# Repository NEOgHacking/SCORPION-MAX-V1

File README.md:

# 3D printer / CNC Mainboard

A main board for a 3d printer or CNC with wide possibilities with the use of the expansion board and thermistor boards! This board is based on the STM32H743 for its massive power. And everyone hates loud stepper motors, so it uses the TMC2130 silent stepper drivers, these are not only very quiet but have a lot of other functions!

# Video of working

# Reason
So long story longer I have an ultimaker 2+ laying at home doing nothing because of the noisy stepper drivers and recently getting an ultimaker S5 so I wanted to make it quieter and more useful. I was amazed by the Prusa mini being so quiet, so I thought why not build my own mainboard with way more quiet stepper drivers and more functions. The second reason is that I am planning to build a CNC somewhere in the future so I thought it would be a genius idea to build my own 3D printer / CNC mainboard with my own overkill specs and the best stepper drivers. And most of all A LOT of power in amps and compute!

# Specs
5x Stepper driver TMC2130

4x Power Mosfets for controlling heated beds, heaters, ext.

4x Fan controller with tacho input

4x Limit switches for homing

3x Thermistor inputs with possibilities for NTC's and PTC's
  These possibilities are possible because of the 2 thermistor boards I have designed, and the NTC thermistor board has a solder jumper to select the resistance of you NTC.

2x Safety inputs for disabling cutting power via a relay to the stepper drivers and mosfets

Expansion port for displays, SD cards, ext.

STM32H743VIT6 for big storage and calculation power

Standard 4 pin power connector and 2 pin screw terminal

USB ports, USB-C for programming and external control and USB-A for USB flash drives

# Design
This board is designed with a lot of safety features and well thought out design, it has a safety circuit to cut power to the steppers and heaters, good pcb design, followed design recommendation from datasheets, used the right components, and allot more! The pcb has been designed with the right trace width and good trace layout with no sharp bends. Also have good pcb layout.
# Schematics
There are 3 schematics for this project:
1. Main board
2. Thermistor modules
3. Expansion module

These are way too long to display here (14 pages) so in the PCB folder there in folder for the board you want to see there is a pdf file of the schematic, but here are a few.

# PCB

Main board

Thermistor boards

Expansion board

# Panalization
I have panelized the thermistor boards for better price per board, the panel still is under the 100x100 limit for the 2 dollar offer on jlcpcb so it’s still very cheap. I needed 6 thermistors for 2 boards and minimum order quantity on jlcpcb is 5, so I made a panel.

# Firmware
The firmware provided is Marlin, but I plan to expand this to more firmware’s like Clipper ext. The board is based on the STM32H743 so it's very powerful and can run almost any firmware!

# BOM
I have made a BOM for LCSC and a global BOM for all the parts and PCBs these are in the BOM folder
The price of the LCSC BOM for all the parts is about 180 dollars for 2 boards and the JLCPCB order is at the 54 dollar.
This is not the cheapest board but it does have the most functions!

# Credits
@Kai Pereira for all my random questions regarding PCB design and blueprint custom project. and for telling me long journals are the best, sorry for the short ones at the beginning. whoops.
Henk, someone I know that is way better in PCB design than me that looked over my schematic and layout ext.

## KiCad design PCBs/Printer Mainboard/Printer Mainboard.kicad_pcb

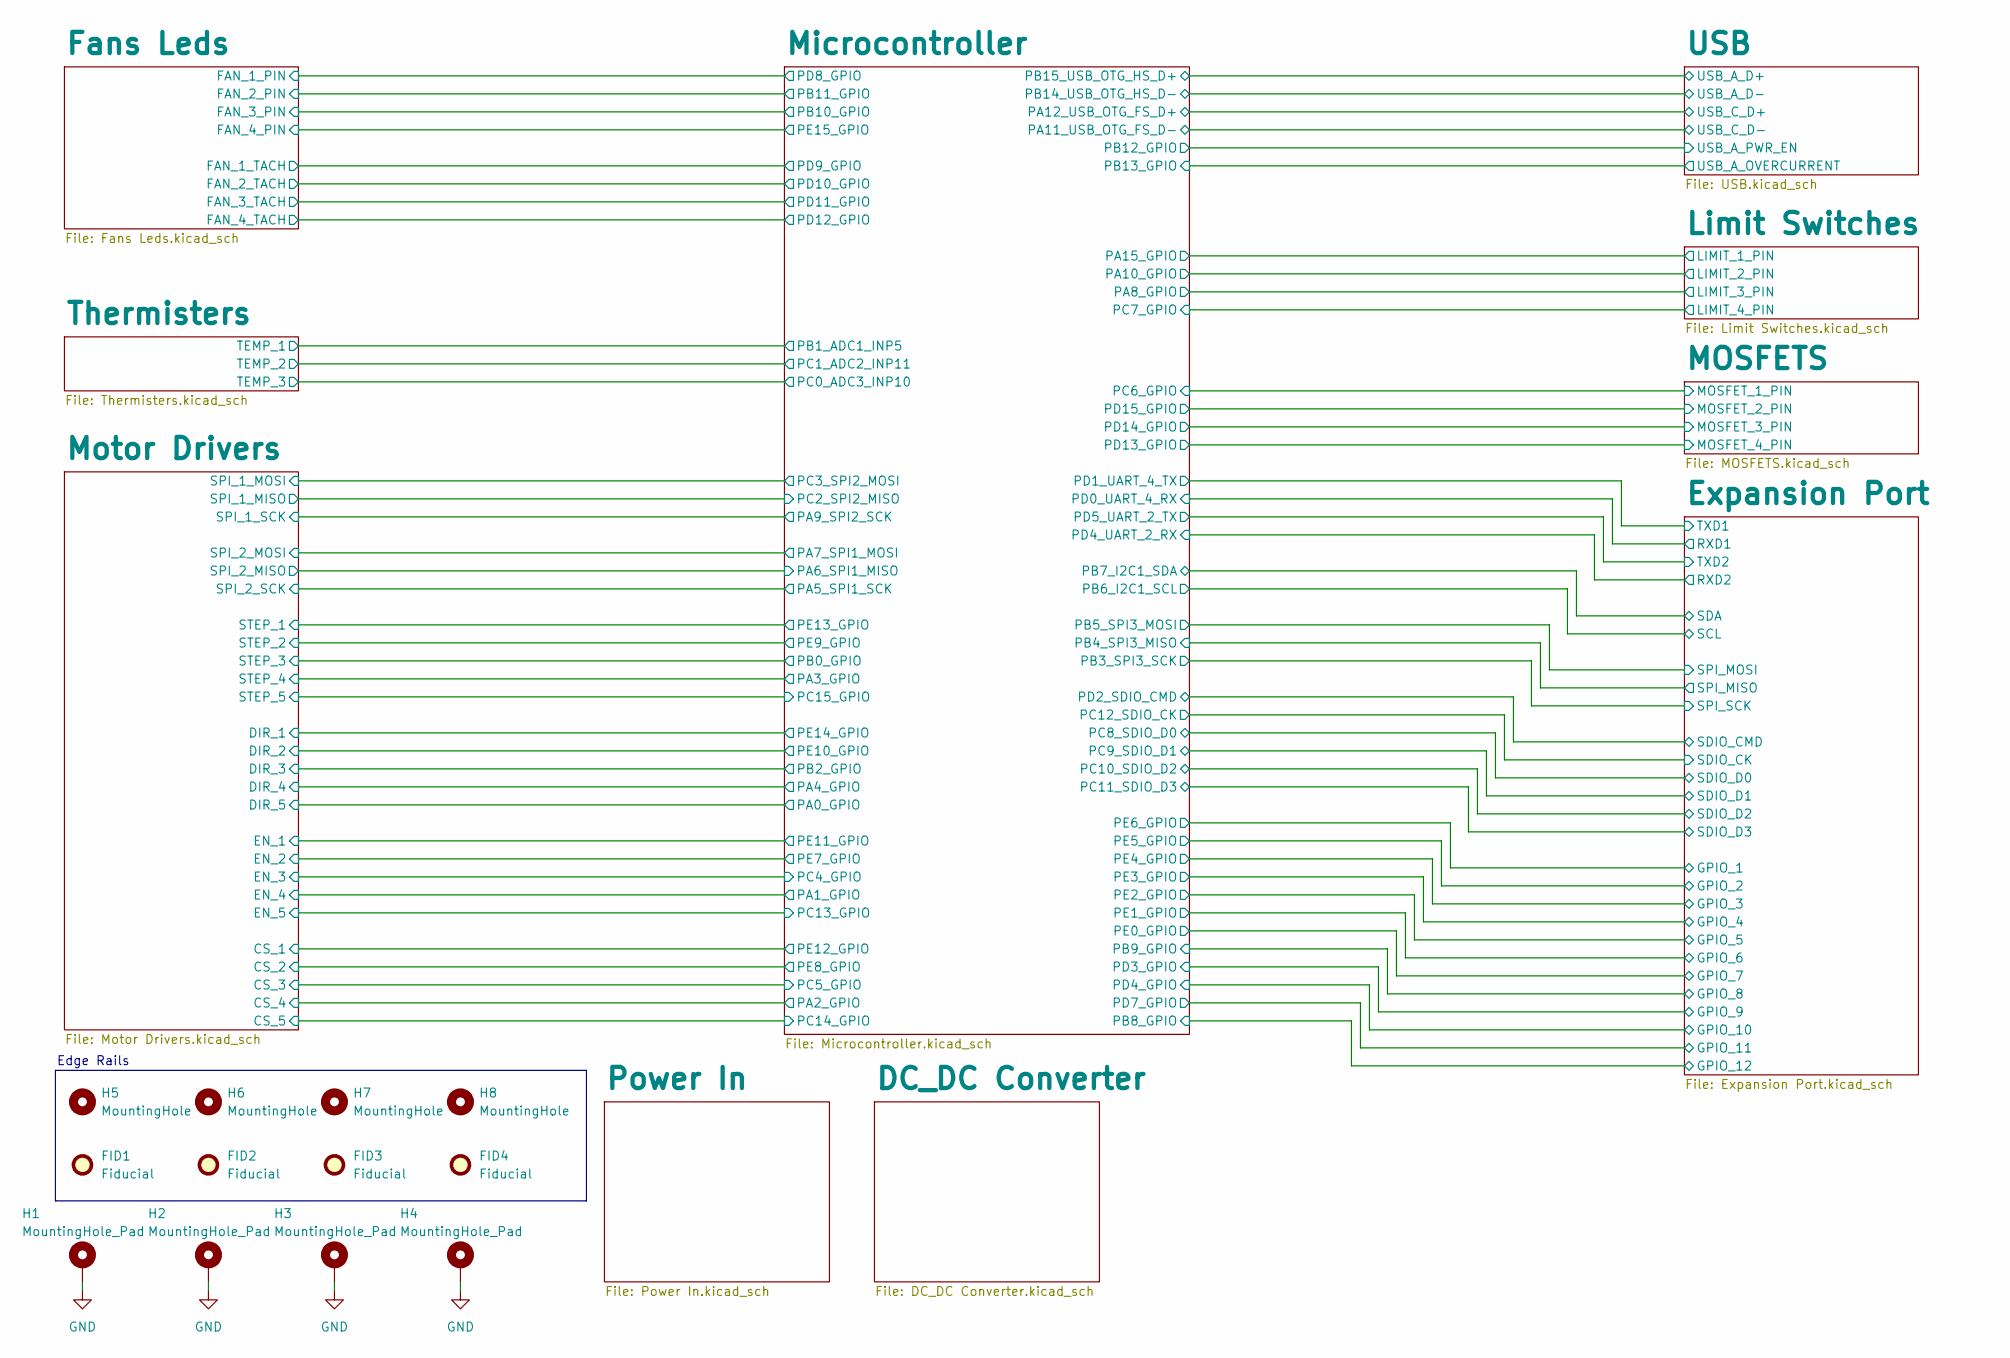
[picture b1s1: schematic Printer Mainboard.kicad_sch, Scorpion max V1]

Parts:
FID1, FID2, FID3, FID4: Fiducial; Fiducial_0.5mm_Mask1.5mm
H1, H2, H3, H4: MountingHole_Pad; MountingHole_3.2mm_M3_Pad
H5, H6, H7, H8: MountingHole; MountingHole_2mm

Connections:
GND: H1.1, H2.1, H3.1, H4.1; also elsewhere on the board

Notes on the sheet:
Edge Rails

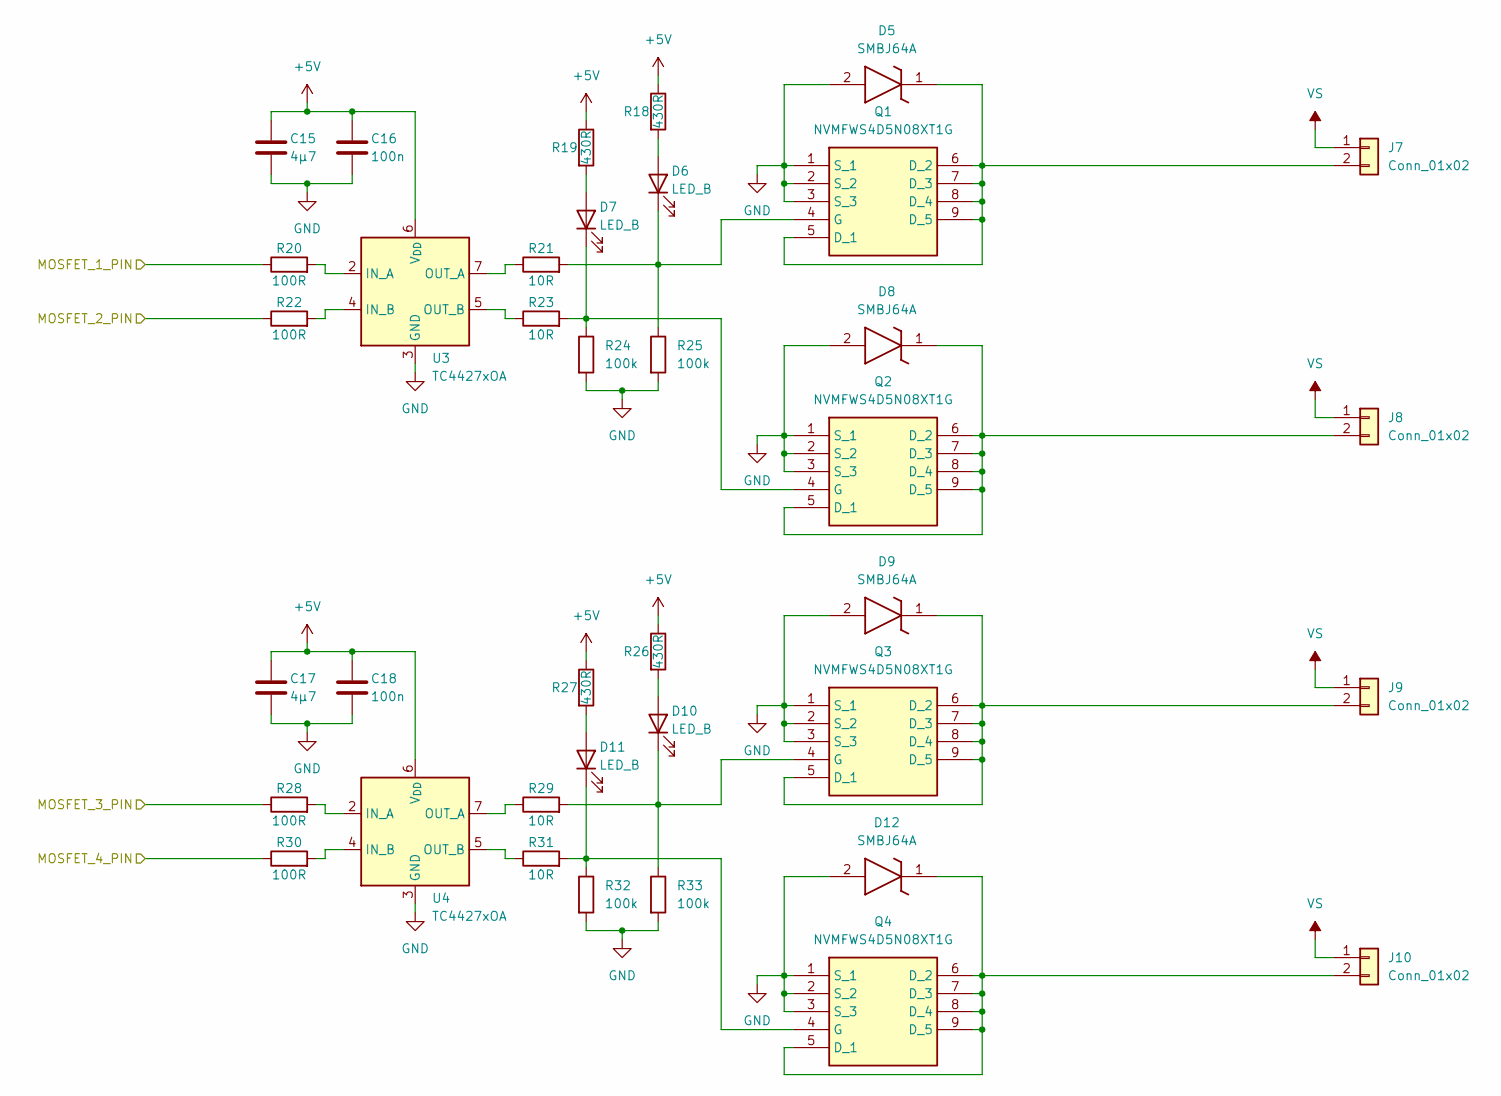
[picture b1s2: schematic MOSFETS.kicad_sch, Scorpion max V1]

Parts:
C15, C17: 4μ7; C_0805_2012Metric
C16, C18: 100n; C_0603_1608Metric
D5, D8, D9, D12: SMBJ64A; DIOM5436X250N; Manufacturer_Part_Number SMBJ64A
D6, D7, D10, D11: LED_B; LED_0603_1608Metric
J7, J8, J9, J10: Conn_01x02; CONN-TH_2P-P5.08_2EDG-5.08-2AW
Q1, Q2, Q3, Q4: NVMFWS4D5N08XT1G; NVMFS5C460NWFT1G; Mouser Part Number 863-NVMFWS4D5N08XT1G
R18, R19, R26, R27: 430R; R_0603_1608Metric
R20, R22, R28, R30: 100R; R_0603_1608Metric
R21, R23, R29, R31: 10R; R_0805_2012Metric
R24, R25, R32, R33: 100k; R_0603_1608Metric
U3, U4: TC4427xOA; SOIC-8_3.9x4.9mm_P1.27mm

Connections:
+5V: C15.1, C16.1, C17.1, C18.1, R18.1, R19.1, R26.1, R27.1, U3.6 (V_{DD}), U4.6 (V_{DD}); also elsewhere on the board
/MOSFETS/MOSFET_1_PIN: R20.1; also elsewhere on the board
/MOSFETS/MOSFET_2_PIN: R22.1; also elsewhere on the board
/MOSFETS/MOSFET_3_PIN: R28.1; also elsewhere on the board
/MOSFETS/MOSFET_4_PIN: R30.1; also elsewhere on the board
GND: C15.2, C16.2, C17.2, C18.2, D5.2 (A), D8.2 (A), D9.2 (A), D12.2 (A), Q1.1 (S_1), Q1.2 (S_2), Q1.3 (S_3), Q2.1 (S_1), Q2.2 (S_2), Q2.3 (S_3), Q3.1 (S_1), Q3.2 (S_2), Q3.3 (S_3), Q4.1 (S_1), Q4.2 (S_2), Q4.3 (S_3), R24.2, R25.2, R32.2, R33.2, U3.3 (GND), U4.3 (GND); also elsewhere on the board
unnamed: D5.1 (K), J7.2, Q1.5 (D_1), Q1.6 (D_2), Q1.7 (D_3), Q1.8 (D_4), Q1.9 (D_5)
unnamed: D6.2 (A), R18.2
unnamed: D6.1 (K), Q1.4 (G), R21.2, R25.1
unnamed: D7.2 (A), R19.2
unnamed: D7.1 (K), Q2.4 (G), R23.2, R24.1
unnamed: D8.1 (K), J8.2, Q2.5 (D_1), Q2.6 (D_2), Q2.7 (D_3), Q2.8 (D_4), Q2.9 (D_5)
unnamed: D9.1 (K), J9.2, Q3.5 (D_1), Q3.6 (D_2), Q3.7 (D_3), Q3.8 (D_4), Q3.9 (D_5)
unnamed: D10.2 (A), R26.2
unnamed: D10.1 (K), Q3.4 (G), R29.2, R33.1
unnamed: D11.2 (A), R27.2
unnamed: D11.1 (K), Q4.4 (G), R31.2, R32.1
unnamed: D12.1 (K), J10.2, Q4.5 (D_1), Q4.6 (D_2), Q4.7 (D_3), Q4.8 (D_4), Q4.9 (D_5)
unnamed: R20.2, U3.2 (IN_A)
unnamed: R22.2, U3.4 (IN_B)
unnamed: R21.1, U3.7 (OUT_A)
unnamed: R23.1, U3.5 (OUT_B)
unnamed: R28.2, U4.2 (IN_A)
unnamed: R30.2, U4.4 (IN_B)
unnamed: R29.1, U4.7 (OUT_A)
unnamed: R31.1, U4.5 (OUT_B)
VS: J7.1, J8.1, J9.1, J10.1; also elsewhere on the board

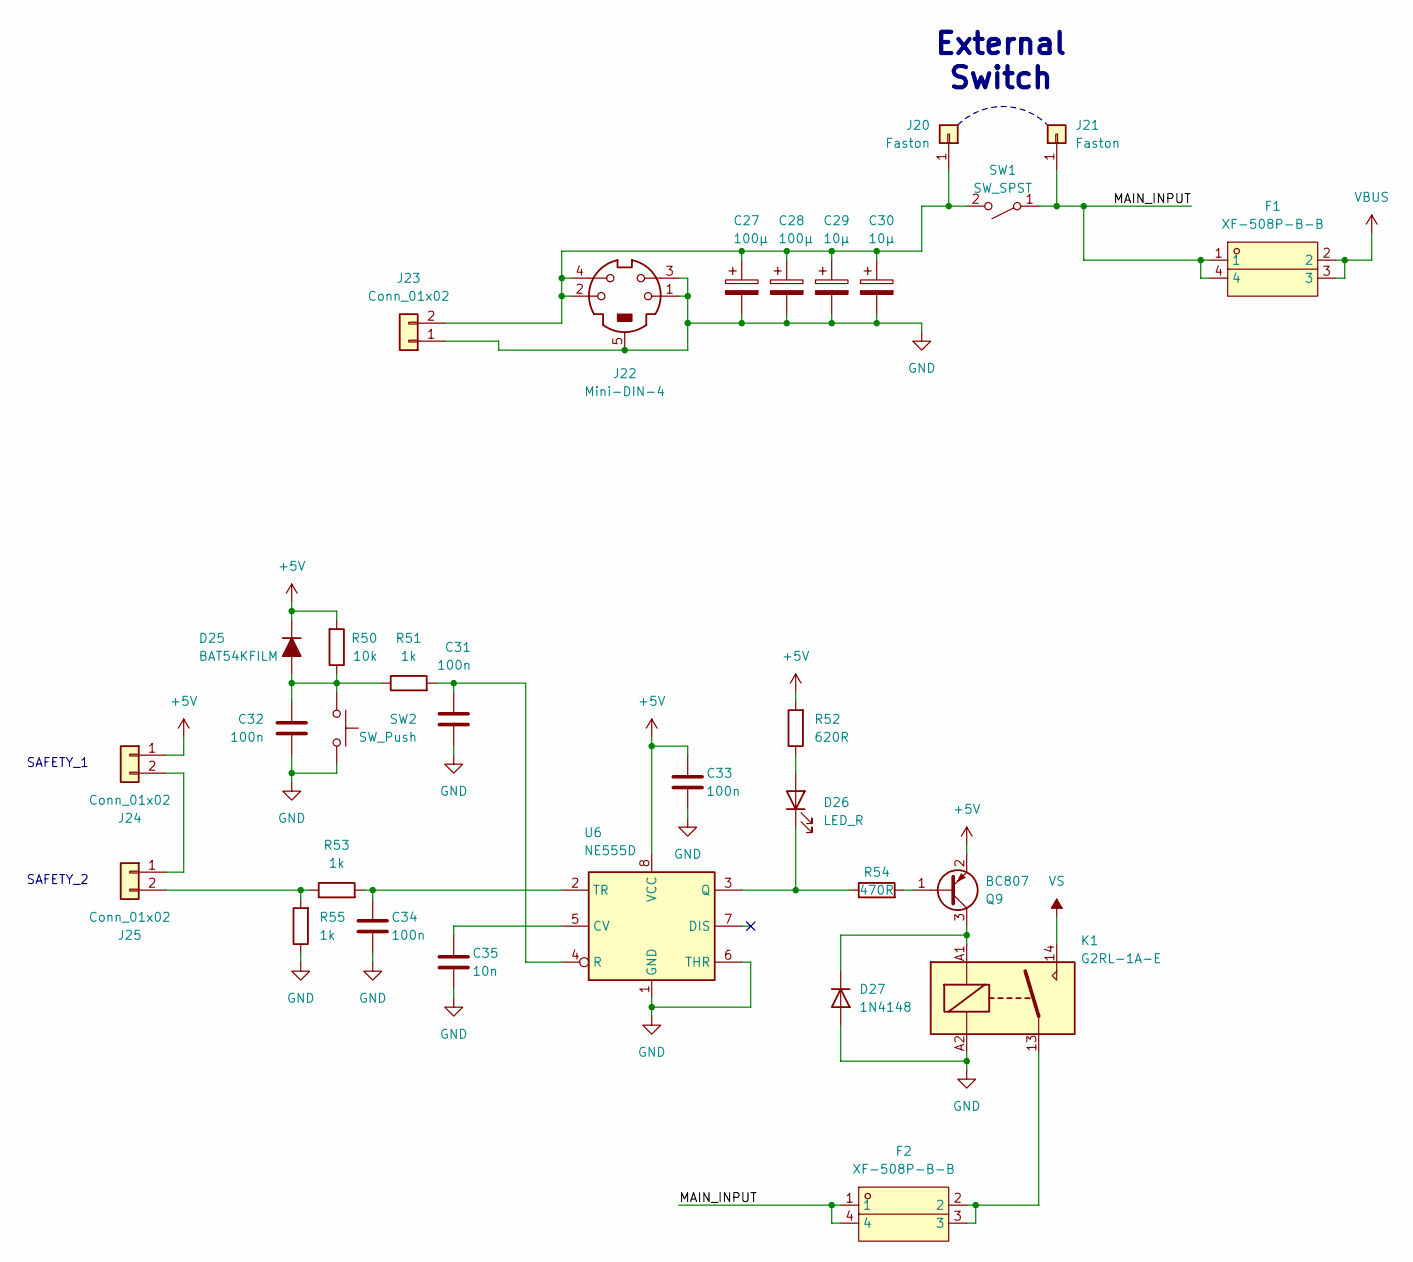
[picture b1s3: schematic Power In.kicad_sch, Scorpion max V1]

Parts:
C27, C28: 100μ; CP_Elec_10x10
C29, C30: 10μ; CP_Elec_6.3x5.8
C31, C32, C33, C34: 100n; C_0603_1608Metric
C35: 10n; C_0603_1608Metric
D25: BAT54KFILM; D_SOD-523
D26: LED_R; LED_0603_1608Metric
D27: 1N4148; D_SOD-523
F1, F2: XF-508P-B-B; FUSE-TH_4P-L16.0-W6.7; LCSC Part C19727305
J20, J21: Faston; CONN-TH_63849-1
J22: Mini-DIN-4; CONN-TH_DIN-422
J23: Conn_01x02; CONN-TH_MKDS3-2-5.08
J24, J25: Conn_01x02; PinHeader_1x02_P2.54mm_Vertical
K1: G2RL-1A-E; Relay_SPST_Omron_G2RL-1A-E
Q9: BC807; SOT-23
R50: 10k; R_0603_1608Metric
R51, R53, R55: 1k; R_0603_1608Metric
R52: 620R; R_0603_1608Metric
R54: 470R; R_0603_1608Metric
SW1: SW_SPST; SW-TH_SDDJF31100
SW2: SW_Push; B3F3120
U6: NE555D; SOIC-8_3.9x4.9mm_P1.27mm

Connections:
+5V: C33.1, D25.1 (K), J24.1, Q9.2 (E), R50.2, R52.2, U6.8 (VCC); also elsewhere on the board
/Power In/MAIN_INPUT: F1.1, F1.4, F2.1, F2.4, J21.1, SW1.1 (A)
GND: C27.2, C28.2, C29.2, C30.2, C31.2, C32.2, C33.2, C34.2, C35.2, D27.2 (A), J22.1, J22.3, J22.5, J23.1, K1.A2, R55.1, SW2.1, U6.1 (GND), U6.6 (THR); also elsewhere on the board
unnamed: C32.1, D25.2 (A), R50.1, R51.1, SW2.2
unnamed: D26.2 (A), R52.1
unnamed: D26.1 (K), R54.1, U6.3 (Q)
unnamed: D27.1 (K), K1.A1, Q9.3 (C)
unnamed: F2.2, F2.3, K1.13
unnamed: C27.1, C28.1, C29.1, C30.1, J20.1, J22.2, J22.4, J23.2, SW1.2 (B)
unnamed: J24.2, J25.1
unnamed: J25.2, R53.1, R55.2
unnamed: Q9.1 (B), R54.2
unnamed: C35.1, U6.5 (CV)
unnamed: C31.1, R51.2, U6.4 (R)
unnamed: C34.1, R53.2, U6.2 (TR)
VBUS: F1.2, F1.3; also elsewhere on the board
VS: K1.14; also elsewhere on the board

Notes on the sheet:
SAFETY_1
External Switch
SAFETY_2

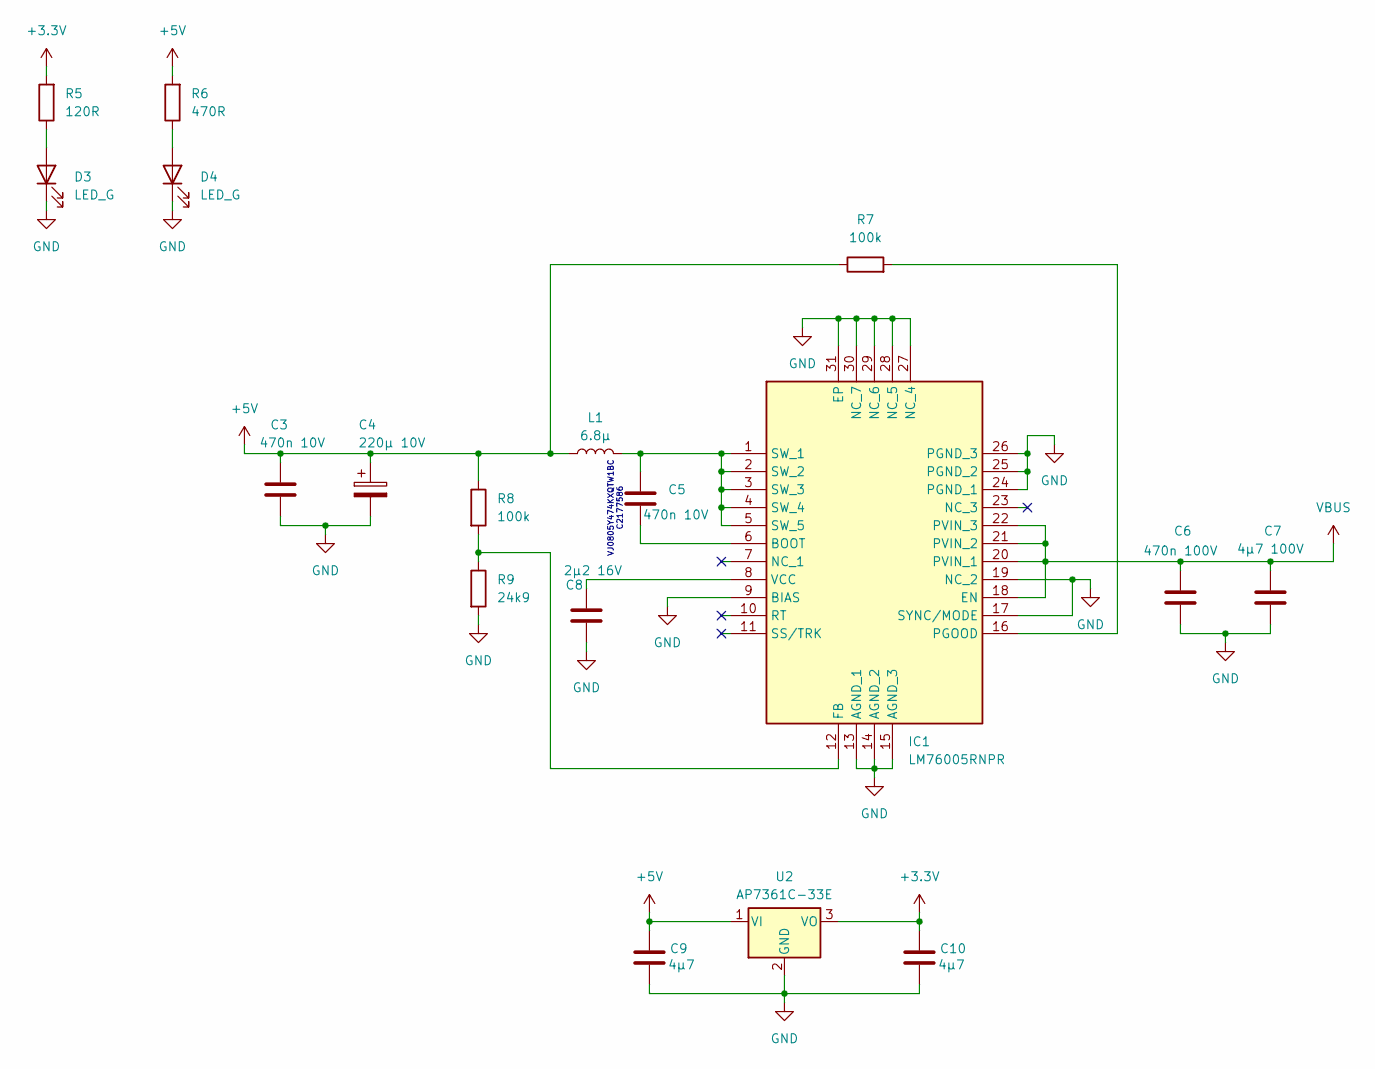
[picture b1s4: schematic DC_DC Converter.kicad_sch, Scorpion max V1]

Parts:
C3, C5: 470n 10V; C_0805_2012Metric
C4: 220μ 10V; CP_EIA-7343-43_Kemet-X
C6: 470n 100V; C_1210_3225Metric
C7: 4μ7 100V; C_1210_3225Metric
C8: 2μ2 16V; C_0603_1608Metric
C9, C10: 4μ7; C_0805_2012Metric
D3, D4: LED_G; LED_0603_1608Metric
IC1: LM76005RNPR; QFN50P400X600X80-31N-D; Mouser Part Number 595-LM76005RNPR
L1: 6.8μ; L_Vishay_IHLP-4040
R5: 120R; R_0603_1608Metric
R6: 470R; R_0603_1608Metric
R7, R8: 100k; R_0603_1608Metric
R9: 24k9; R_0603_1608Metric
U2: AP7361C-33E; SOT-223-3_TabPin2

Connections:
+3.3V: C10.1, R5.2, U2.3 (VO); also elsewhere on the board
+5V: C3.1, C4.1, C9.1, L1.1, R6.2, R7.1, R8.1, U2.1 (VI); also elsewhere on the board
GND: C3.2, C4.2, C6.2, C7.2, C8.2, C9.2, C10.2, D3.1 (K), D4.1 (K), IC1.9 (BIAS), IC1.13 (AGND_1), IC1.14 (AGND_2), IC1.15 (AGND_3), IC1.17 (SYNC/MODE), IC1.19 (NC_2), IC1.24 (PGND_1), IC1.25 (PGND_2), IC1.26 (PGND_3), IC1.27 (NC_4), IC1.28 (NC_5), IC1.29 (NC_6), IC1.30 (NC_7), IC1.31 (EP), R9.2, U2.2 (GND); also elsewhere on the board
unnamed: D3.2 (A), R5.1
unnamed: D4.2 (A), R6.1
unnamed: C5.1, IC1.6 (BOOT)
unnamed: IC1.12 (FB), R8.2, R9.1
unnamed: IC1.16 (PGOOD), R7.2
unnamed: C5.2, IC1.1 (SW_1), IC1.2 (SW_2), IC1.3 (SW_3), IC1.4 (SW_4), IC1.5 (SW_5), L1.2
unnamed: C8.1, IC1.8 (VCC)
VBUS: C6.1, C7.1, IC1.18 (EN), IC1.20 (PVIN_1), IC1.21 (PVIN_2), IC1.22 (PVIN_3); also elsewhere on the board

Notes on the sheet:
VJ0805Y474KXQTW1BC C2177586

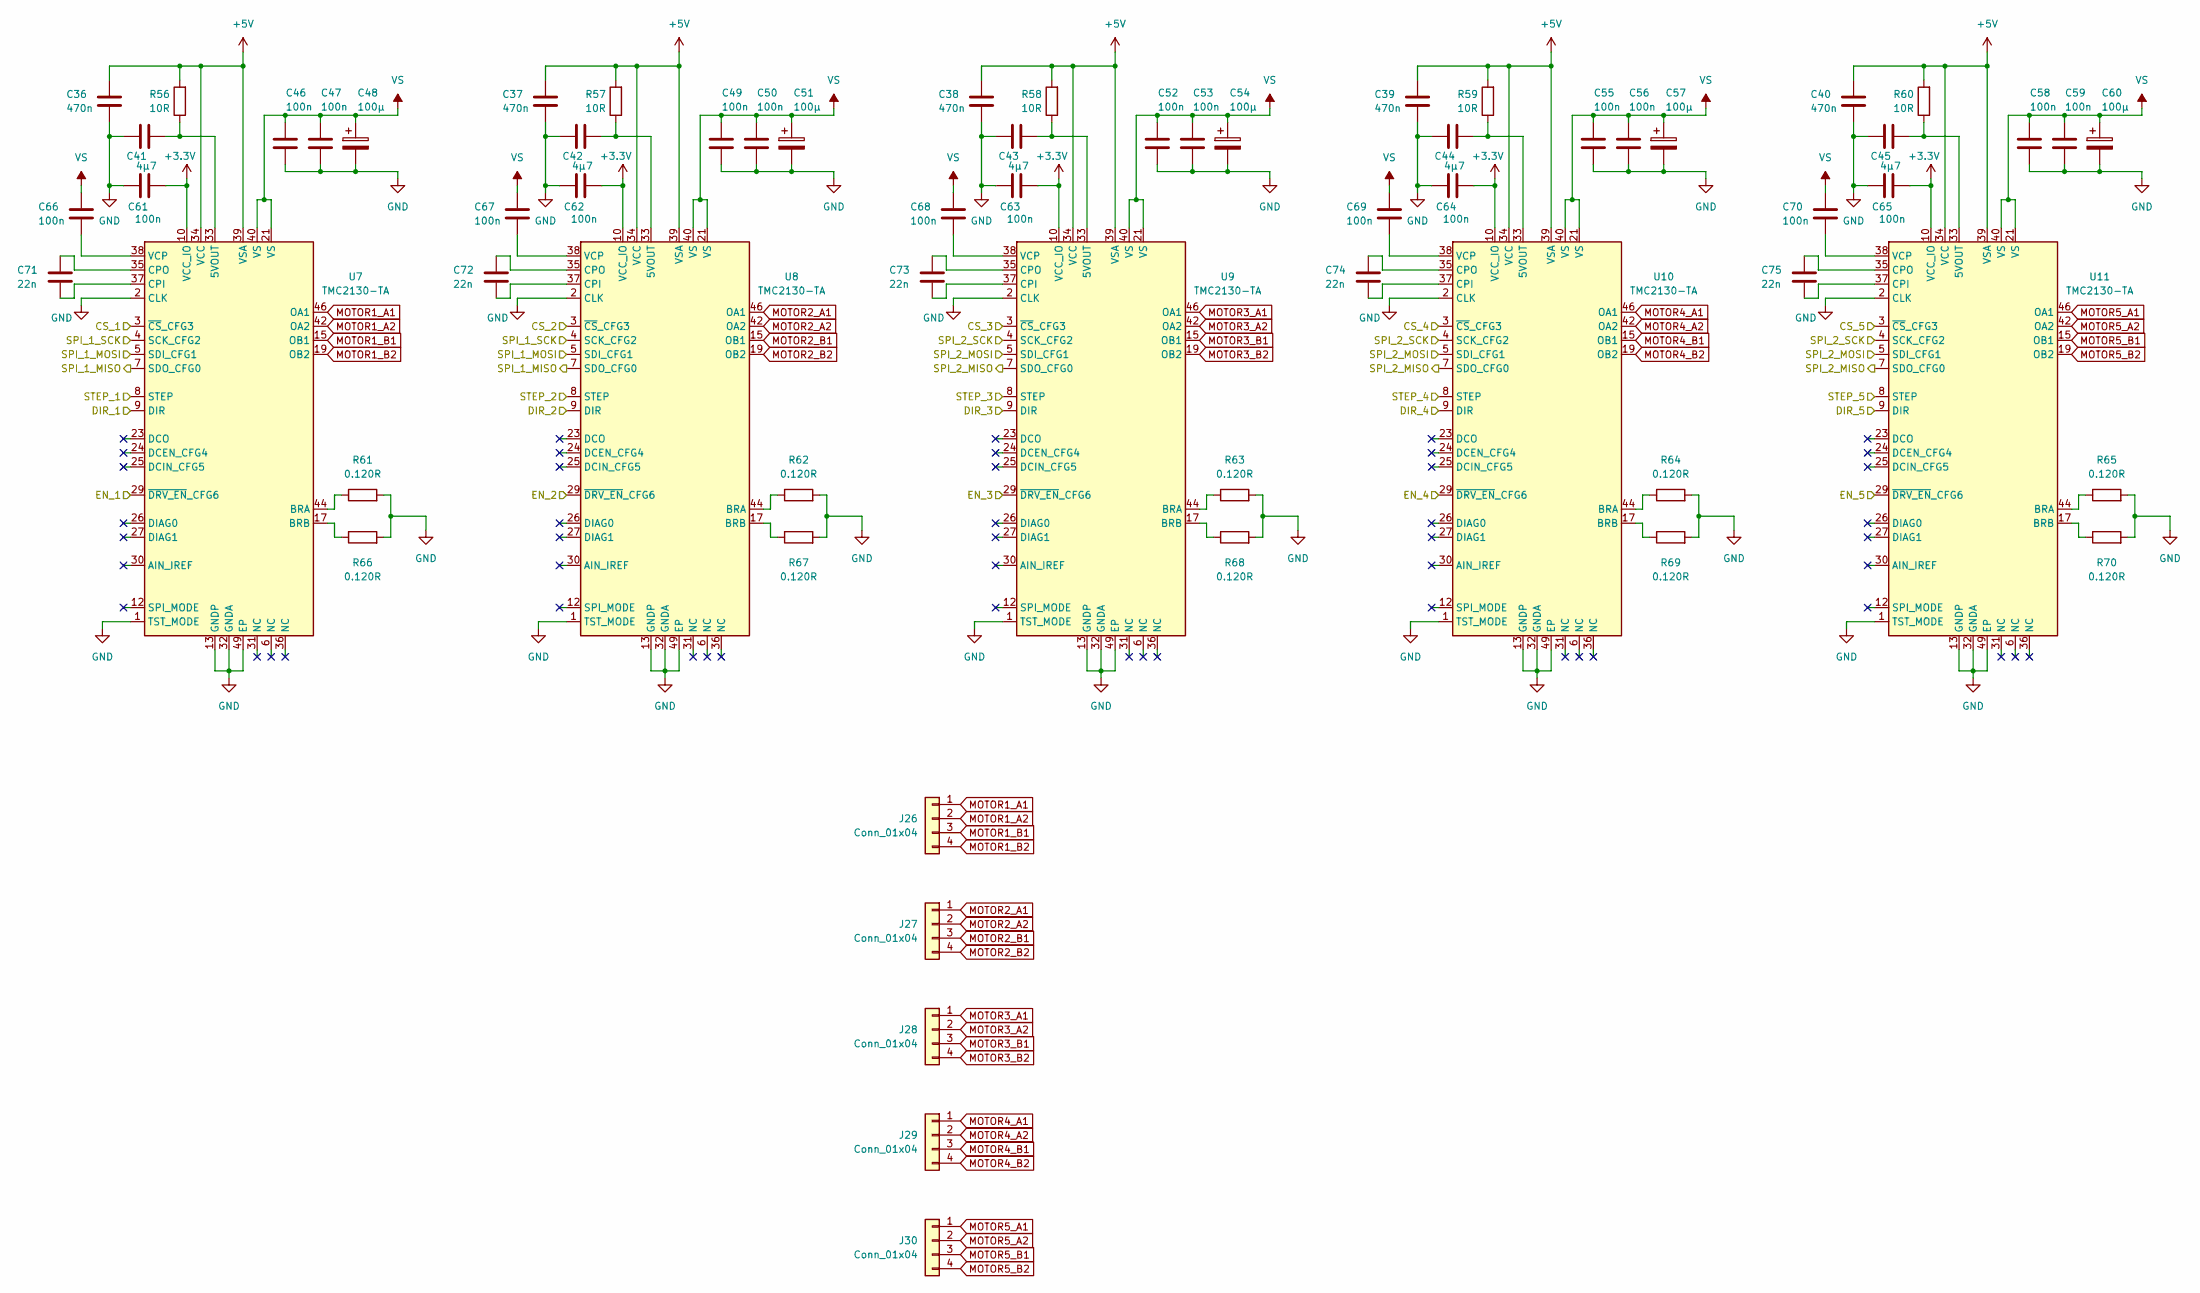
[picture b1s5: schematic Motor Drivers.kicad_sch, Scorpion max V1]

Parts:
C36, C37, C38, C39, C40: 470n; C_0603_1608Metric
C41, C42, C43, C44, C45: 4μ7; C_0805_2012Metric
C46, C47, C49, C50, C52, C53, C55, C56, C58, C59, C61, C62, C63, C64, C65, C66, C67, C68, C69, C70: 100n; C_0603_1608Metric
C48, C51, C54, C57, C60: 100μ; CP_Elec_10x10
C71, C72, C73, C74, C75: 22n; C_0603_1608Metric
J26, J27, J28, J29, J30: Conn_01x04; JST_XH_B4B-XH-A_1x04_P2.50mm_Vertical
R56, R57, R58, R59, R60: 10R; R_0603_1608Metric
R61, R62, R63, R64, R65, R66, R67, R68, R69, R70: 0.120R; R_1206_3216Metric
U7, U8, U9, U10, U11: TMC2130-TA; TQFP-48-1EP_7x7mm_P0.5mm_EP5x5mm_ThermalVias

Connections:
+3.3V: C61.1, C62.1, C63.1, C64.1, C65.1, U7.10 (VCC_IO), U8.10 (VCC_IO), U9.10 (VCC_IO), U10.10 (VCC_IO), U11.10 (VCC_IO); also elsewhere on the board
+5V: C36.2, C37.2, C38.2, C39.2, C40.2, R56.2, R57.2, R58.2, R59.2, R60.2, U7.34 (VCC), U7.39 (VSA), U8.34 (VCC), U8.39 (VSA), U9.34 (VCC), U9.39 (VSA), U10.34 (VCC), U10.39 (VSA), U11.34 (VCC), U11.39 (VSA); also elsewhere on the board
/Microcontroller/PA0_GPIO: U11.9 (DIR); also elsewhere on the board
/Microcontroller/PA1_GPIO: U10.29 (~DRV_EN_CFG6); also elsewhere on the board
/Microcontroller/PA2_GPIO: U10.3 (~CS_CFG3); also elsewhere on the board
/Microcontroller/PA3_GPIO: U10.8 (STEP); also elsewhere on the board
/Microcontroller/PA4_GPIO: U10.9 (DIR); also elsewhere on the board
/Microcontroller/PA5_SPI1_SCK: U9.4 (SCK_CFG2), U10.4 (SCK_CFG2), U11.4 (SCK_CFG2); also elsewhere on the board
/Microcontroller/PA6_SPI1_MISO: U9.7 (SDO_CFG0), U10.7 (SDO_CFG0), U11.7 (SDO_CFG0); also elsewhere on the board
/Microcontroller/PA7_SPI1_MOSI: U9.5 (SDI_CFG1), U10.5 (SDI_CFG1), U11.5 (SDI_CFG1); also elsewhere on the board
/Microcontroller/PA9_SPI2_SCK: U7.4 (SCK_CFG2), U8.4 (SCK_CFG2); also elsewhere on the board
/Microcontroller/PB0_GPIO: U9.8 (STEP); also elsewhere on the board
/Microcontroller/PB2_GPIO: U9.9 (DIR); also elsewhere on the board
/Microcontroller/PC2_SPI2_MISO: U7.7 (SDO_CFG0), U8.7 (SDO_CFG0); also elsewhere on the board
/Microcontroller/PC3_SPI2_MOSI: U7.5 (SDI_CFG1), U8.5 (SDI_CFG1); also elsewhere on the board
/Microcontroller/PC4_GPIO: U9.29 (~DRV_EN_CFG6); also elsewhere on the board
/Microcontroller/PC5_GPIO: U9.3 (~CS_CFG3); also elsewhere on the board
/Microcontroller/PC13_GPIO: U11.29 (~DRV_EN_CFG6); also elsewhere on the board
/Microcontroller/PC14_GPIO: U11.3 (~CS_CFG3); also elsewhere on the board
/Microcontroller/PC15_GPIO: U11.8 (STEP); also elsewhere on the board
/Microcontroller/PE7_GPIO: U8.29 (~DRV_EN_CFG6); also elsewhere on the board
/Microcontroller/PE8_GPIO: U8.3 (~CS_CFG3); also elsewhere on the board
/Microcontroller/PE9_GPIO: U8.8 (STEP); also elsewhere on the board
/Microcontroller/PE10_GPIO: U8.9 (DIR); also elsewhere on the board
/Microcontroller/PE11_GPIO: U7.29 (~DRV_EN_CFG6); also elsewhere on the board
/Microcontroller/PE12_GPIO: U7.3 (~CS_CFG3); also elsewhere on the board
/Microcontroller/PE13_GPIO: U7.8 (STEP); also elsewhere on the board
/Microcontroller/PE14_GPIO: U7.9 (DIR); also elsewhere on the board
GND: C36.1, C37.1, C38.1, C39.1, C40.1, C41.2, C42.2, C43.2, C44.2, C45.2, C46.1, C47.1, C48.2, C49.1, C50.1, C51.2, C52.1, C53.1, C54.2, C55.1, C56.1, C57.2, C58.1, C59.1, C60.2, C61.2, C62.2, C63.2, C64.2, C65.2, R61.2, R62.2, R63.2, R64.2, R65.2, R66.2, R67.2, R68.2, R69.2, R70.2, U7.1 (TST_MODE), U7.2 (CLK), U7.13 (GNDP), U7.32 (GNDA), U7.48 (GNDP), U7.49 (EP), U8.1 (TST_MODE), U8.2 (CLK), U8.13 (GNDP), U8.32 (GNDA), U8.48 (GNDP), U8.49 (EP), U9.1 (TST_MODE), U9.2 (CLK), U9.13 (GNDP), U9.32 (GNDA), U9.48 (GNDP), U9.49 (EP), U10.1 (TST_MODE), U10.2 (CLK), U10.13 (GNDP), U10.32 (GNDA), U10.48 (GNDP), U10.49 (EP), U11.1 (TST_MODE), U11.2 (CLK), U11.13 (GNDP), U11.32 (GNDA), U11.48 (GNDP), U11.49 (EP); also elsewhere on the board
MOTOR1_A1: J26.1, U7.46 (OA1)
MOTOR1_A2: J26.2, U7.42 (OA2)
MOTOR1_B1: J26.3, U7.15 (OB1)
MOTOR1_B2: J26.4, U7.19 (OB2)
MOTOR2_A1: J27.1, U8.46 (OA1)
MOTOR2_A2: J27.2, U8.42 (OA2)
MOTOR2_B1: J27.3, U8.15 (OB1)
MOTOR2_B2: J27.4, U8.19 (OB2)
MOTOR3_A1: J28.1, U9.46 (OA1)
MOTOR3_A2: J28.2, U9.42 (OA2)
MOTOR3_B1: J28.3, U9.15 (OB1)
MOTOR3_B2: J28.4, U9.19 (OB2)
MOTOR4_A1: J29.1, U10.46 (OA1)
MOTOR4_A2: J29.2, U10.42 (OA2)
MOTOR4_B1: J29.3, U10.15 (OB1)
MOTOR4_B2: J29.4, U10.19 (OB2)
MOTOR5_A1: J30.1, U11.46 (OA1)
MOTOR5_A2: J30.2, U11.42 (OA2)
MOTOR5_B1: J30.3, U11.15 (OB1)
MOTOR5_B2: J30.4, U11.19 (OB2)
unnamed: C41.1, R56.1, U7.33 (5VOUT)
unnamed: R61.1, U7.44 (BRA)
unnamed: R66.1, U7.17 (BRB)
unnamed: C71.1, U7.37 (CPI)
unnamed: C71.2, U7.35 (CPO)
unnamed: C66.1, U7.38 (VCP)
unnamed: C42.1, R57.1, U8.33 (5VOUT)
unnamed: R62.1, U8.44 (BRA)
unnamed: R67.1, U8.17 (BRB)
unnamed: C72.1, U8.37 (CPI)
unnamed: C72.2, U8.35 (CPO)
unnamed: C67.1, U8.38 (VCP)
unnamed: C43.1, R58.1, U9.33 (5VOUT)
unnamed: R63.1, U9.44 (BRA)
unnamed: R68.1, U9.17 (BRB)
unnamed: C73.1, U9.37 (CPI)
unnamed: C73.2, U9.35 (CPO)
unnamed: C68.1, U9.38 (VCP)
unnamed: C44.1, R59.1, U10.33 (5VOUT)
unnamed: R64.1, U10.44 (BRA)
unnamed: R69.1, U10.17 (BRB)
unnamed: C74.1, U10.37 (CPI)
unnamed: C74.2, U10.35 (CPO)
unnamed: C69.1, U10.38 (VCP)
unnamed: C45.1, R60.1, U11.33 (5VOUT)
unnamed: R65.1, U11.44 (BRA)
unnamed: R70.1, U11.17 (BRB)
unnamed: C75.1, U11.37 (CPI)
unnamed: C75.2, U11.35 (CPO)
unnamed: C70.1, U11.38 (VCP)
VS: C46.2, C47.2, C48.1, C49.2, C50.2, C51.1, C52.2, C53.2, C54.1, C55.2, C56.2, C57.1, C58.2, C59.2, C60.1, C66.2, C67.2, C68.2, C69.2, C70.2, U7.21 (VS), U7.40 (VS), U8.21 (VS), U8.40 (VS), U9.21 (VS), U9.40 (VS), U10.21 (VS), U10.40 (VS), U11.21 (VS), U11.40 (VS); also elsewhere on the board

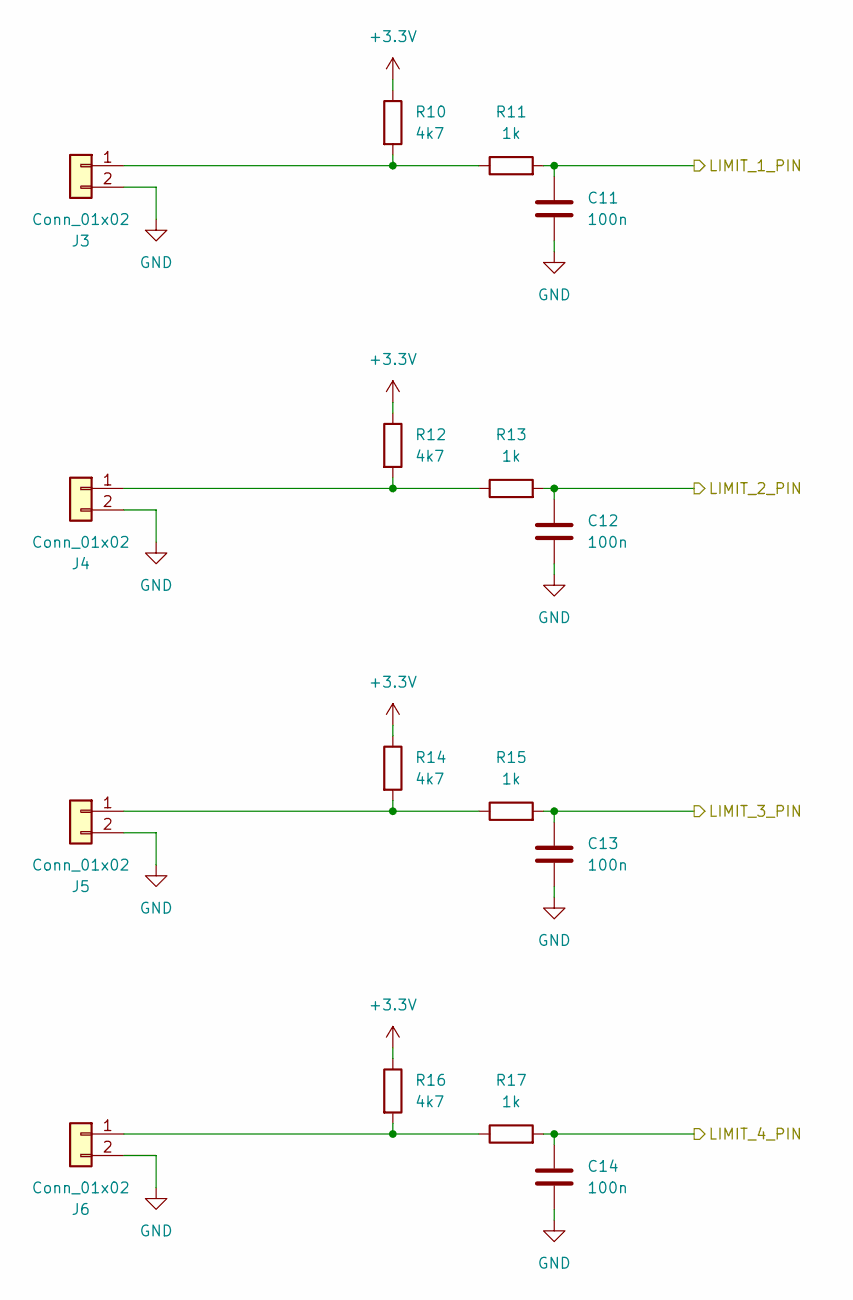
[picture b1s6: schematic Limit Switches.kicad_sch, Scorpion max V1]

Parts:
C11, C12, C13, C14: 100n; C_0603_1608Metric
J3, J4, J5, J6: Conn_01x02; JST_XH_B2B-XH-A_1x02_P2.50mm_Vertical
R10, R12, R14, R16: 4k7; R_0603_1608Metric
R11, R13, R15, R17: 1k; R_0603_1608Metric

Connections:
+3.3V: R10.1, R12.1, R14.1, R16.1; also elsewhere on the board
/Limit Switches/LIMIT_1_PIN: C11.1, R11.2; also elsewhere on the board
/Limit Switches/LIMIT_2_PIN: C12.1, R13.2; also elsewhere on the board
/Limit Switches/LIMIT_3_PIN: C13.1, R15.2; also elsewhere on the board
/Limit Switches/LIMIT_4_PIN: C14.1, R17.2; also elsewhere on the board
GND: C11.2, C12.2, C13.2, C14.2, J3.2, J4.2, J5.2, J6.2; also elsewhere on the board
unnamed: J3.1, R10.2, R11.1
unnamed: J4.1, R12.2, R13.1
unnamed: J5.1, R14.2, R15.1
unnamed: J6.1, R16.2, R17.1
